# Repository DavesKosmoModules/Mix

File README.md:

# Mix

A 50mm Simple Mixer

- 5 inputs
- 1 output
- gain between 0 - 2

Contained are schematics & gerber files for pcb fabrication of both electrical and front panel. This is sutiable for entry level however a basic level of electronics, soldering, fault finding, and some basic tools are required.

[Schematic](/Docs/Mix-Schematic.pdf)

[BOM](Docs/Mix-BOM.pdf)

If you wish to edit in ki-cad the following dependencies are required

 https://github.com/holmesrichards/Kosmo_panel
 
 https://github.com/holmesrichards/aoKicad

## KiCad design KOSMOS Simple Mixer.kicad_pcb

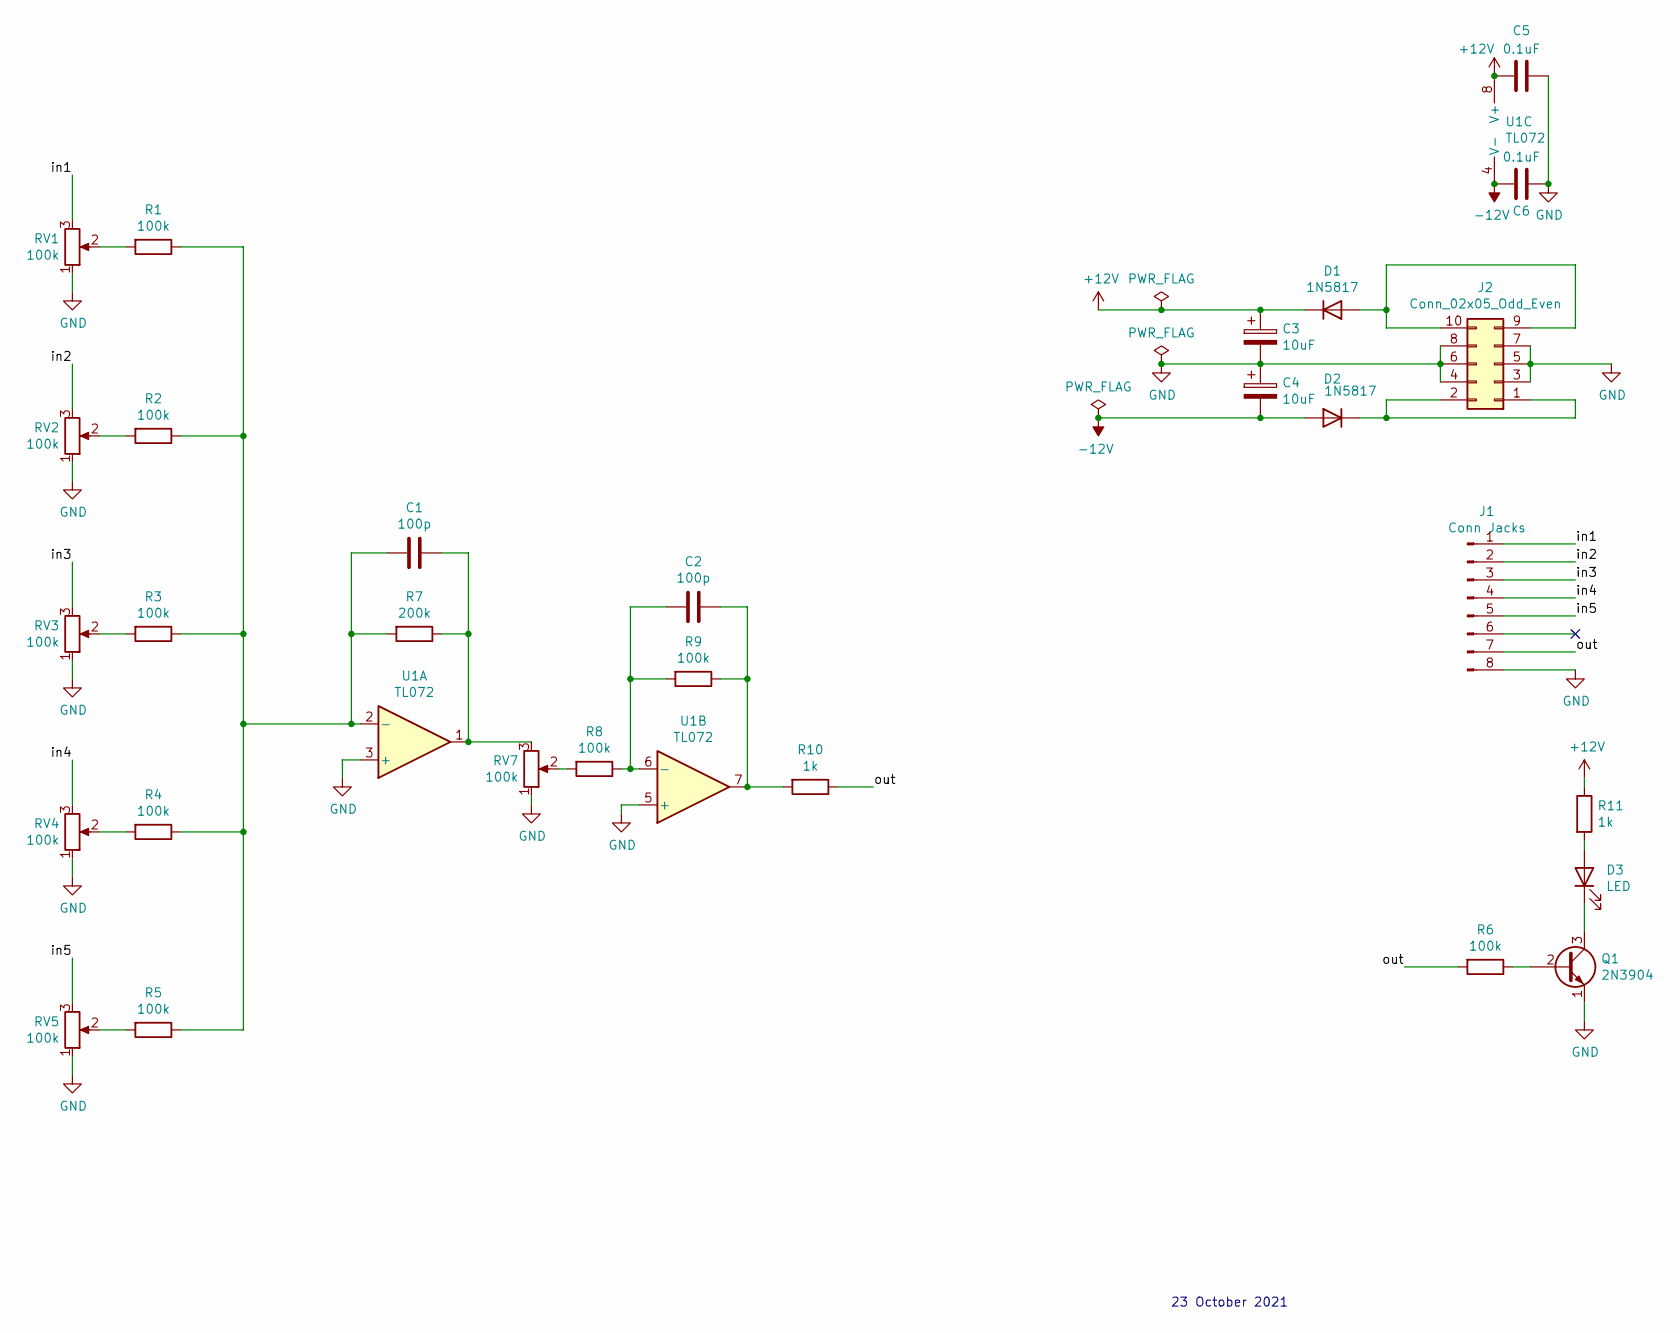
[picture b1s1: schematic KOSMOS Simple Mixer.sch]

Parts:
C1, C2: 100p; C_Disc_D3.0mm_W1.6mm_P2.50mm
C3, C4: 10uF; CP_Radial_D6.3mm_P2.50mm
C5, C6: 0.1uF; C_Disc_D3.0mm_W1.6mm_P2.50mm
D1, D2: 1N5817; D_DO-41_SOD81_P10.16mm_Horizontal
D3: LED; LED_D5.0mm
J1: Conn Jacks; PinHeader_1x08_P2.54mm_Vertical
J2: Conn_02x05_Odd_Even; Power_Header
Q1: 2N3904; TO-92_Inline_Wide
R1, R2, R3, R4, R5, R6, R8, R9: 100k; R_Axial_DIN0207_L6.3mm_D2.5mm_P10.16mm_Horizontal
R7: 200k; R_Axial_DIN0207_L6.3mm_D2.5mm_P10.16mm_Horizontal
R10, R11: 1k; R_Axial_DIN0207_L6.3mm_D2.5mm_P10.16mm_Horizontal
RV1, RV2, RV3, RV4, RV5, RV7: 100k; Potentiometer_Alpha_RD901F-40-00D_Single_Vertical_CircularH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
U1: TL072; DIP-8_W7.62mm_Socket_LongPads

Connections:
+12V: C3.1, C5.2, D1.1 (K), R11.1, U1.8 (V+)
-12V: C4.2, C6.2, D2.2 (A), U1.4 (V-)
/in1: J1.1, RV1.3
/in2: J1.2, RV2.3
/in3: J1.3, RV3.3
/in4: J1.4, RV4.3
/in5: J1.5, RV5.3
/out: J1.7, R6.2, R10.1
GND: C3.2, C4.1, C5.1, C6.1, J1.8, J2.3, J2.4, J2.5, J2.6, J2.7, J2.8, Q1.1 (E), RV1.1, RV2.1, RV3.1, RV4.1, RV5.1, RV7.1, U1.3 (+), U1.5 (+)
unnamed: C1.1, R7.1, RV7.3, U1.1
unnamed: C1.2, R1.1, R2.1, R3.1, R4.1, R5.1, R7.2, U1.2 (-)
unnamed: C2.1, R9.1, R10.2, U1.7
unnamed: C2.2, R8.1, R9.2, U1.6 (-)
unnamed: D1.2 (A), J2.9, J2.10
unnamed: D2.1 (K), J2.1, J2.2
unnamed: D3.1 (K), Q1.3 (C)
unnamed: D3.2 (A), R11.2
unnamed: Q1.2 (B), R6.1
unnamed: R1.2, RV1.2
unnamed: R2.2, RV2.2
unnamed: R3.2, RV3.2
unnamed: R4.2, RV4.2
unnamed: R5.2, RV5.2
unnamed: R8.2, RV7.2

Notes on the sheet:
23 October 2021

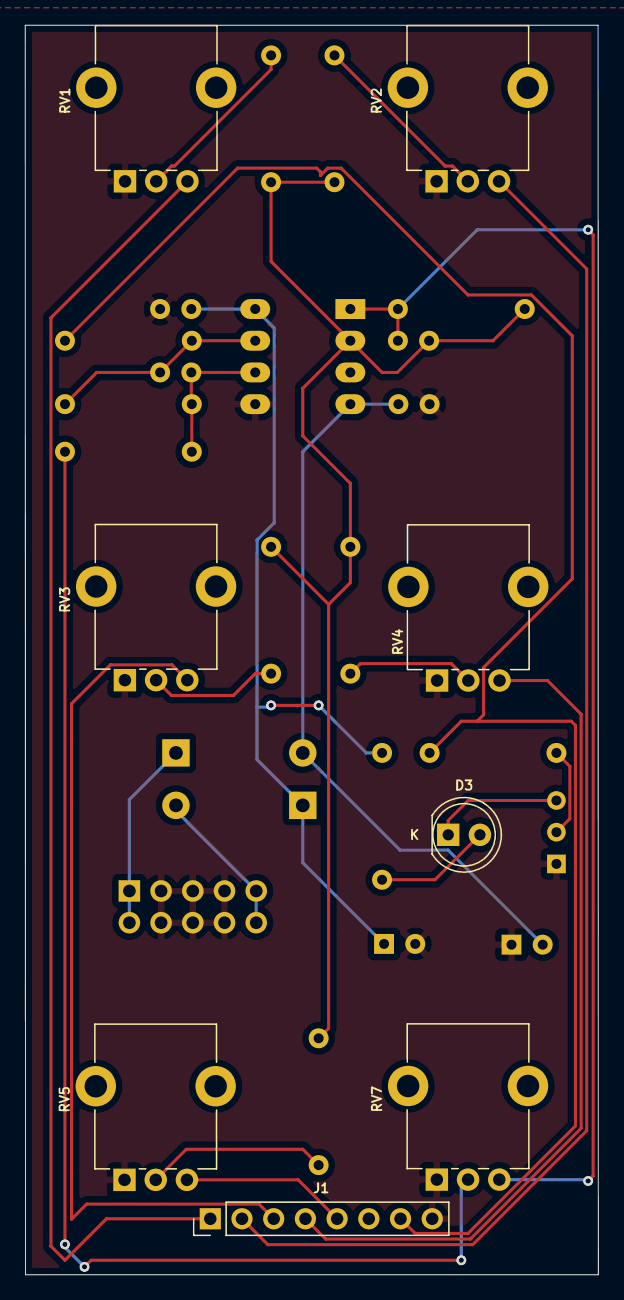
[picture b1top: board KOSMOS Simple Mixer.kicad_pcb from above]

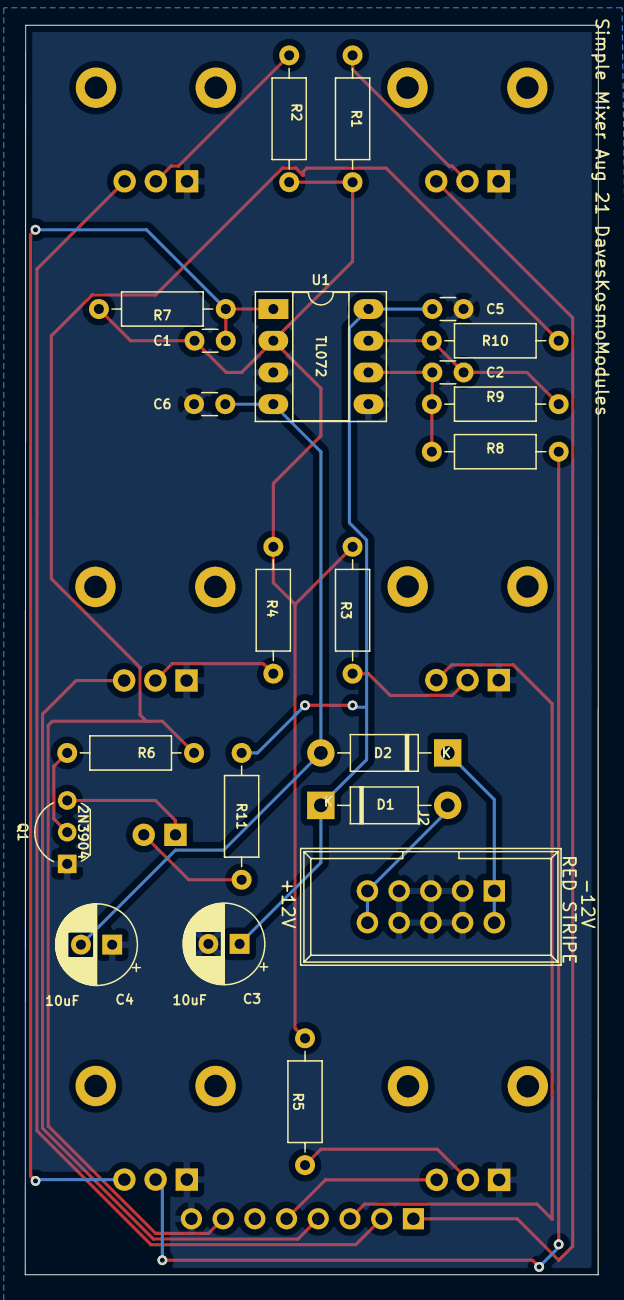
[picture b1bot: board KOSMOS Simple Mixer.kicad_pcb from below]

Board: 2 copper layers, 45.9 x 100.1 mm, 30 parts (22 on the bottom side), 24 nets.

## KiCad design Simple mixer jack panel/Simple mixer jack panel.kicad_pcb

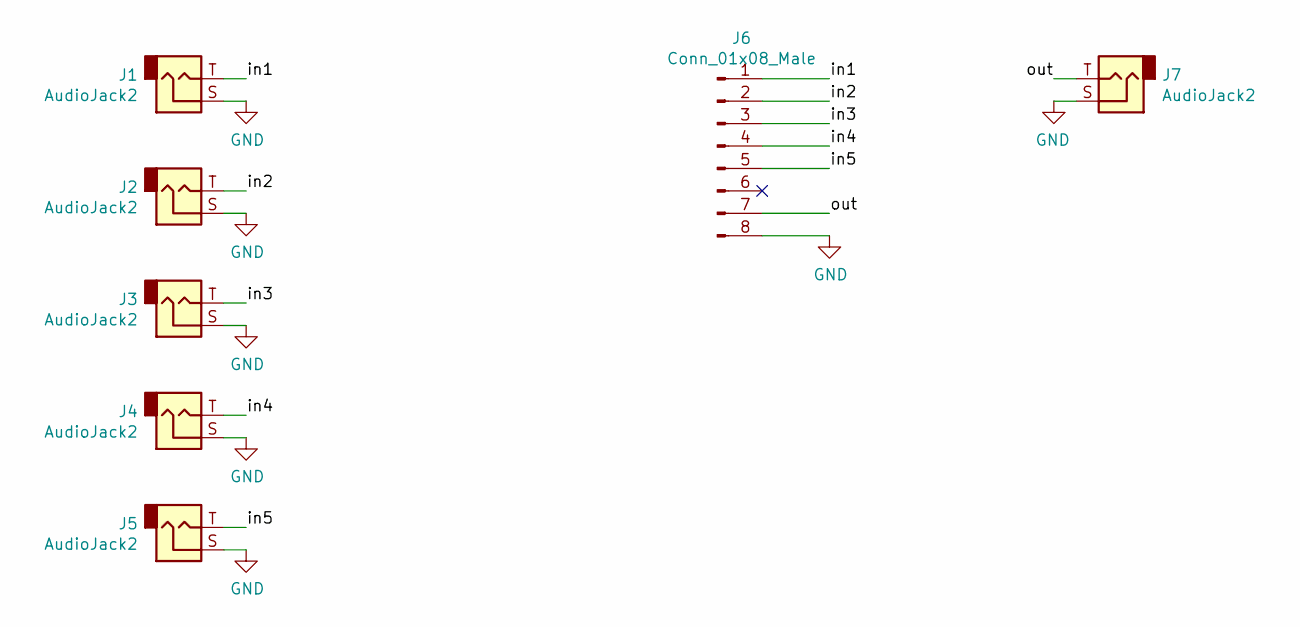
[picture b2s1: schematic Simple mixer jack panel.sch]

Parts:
J1, J2, J3, J4, J5, J7: AudioJack2; Jack_6.35mm_PJ_629HAN
J6: Conn_01x08_Male; PinHeader_1x08_P2.54mm_Vertical

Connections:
/in1: J1.T, J6.1
/in2: J2.T, J6.2
/in3: J3.T, J6.3
/in4: J4.T, J6.4
/in5: J5.T, J6.5
/out: J6.7, J7.T
GND: J1.S, J2.S, J3.S, J4.S, J5.S, J6.8, J7.S

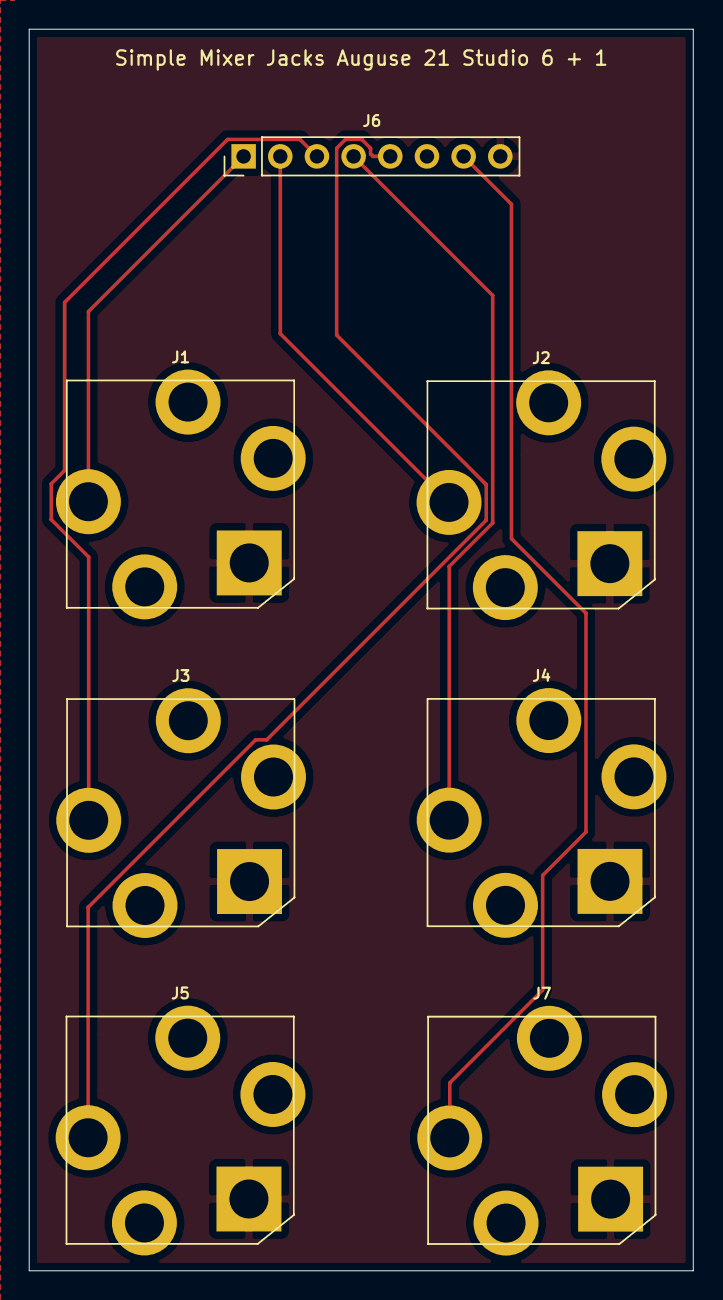
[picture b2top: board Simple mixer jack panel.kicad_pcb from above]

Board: 2 copper layers, 46.0 x 86.0 mm, 7 parts (0 on the bottom side), 7 nets.

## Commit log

2021-10-23 Initial
